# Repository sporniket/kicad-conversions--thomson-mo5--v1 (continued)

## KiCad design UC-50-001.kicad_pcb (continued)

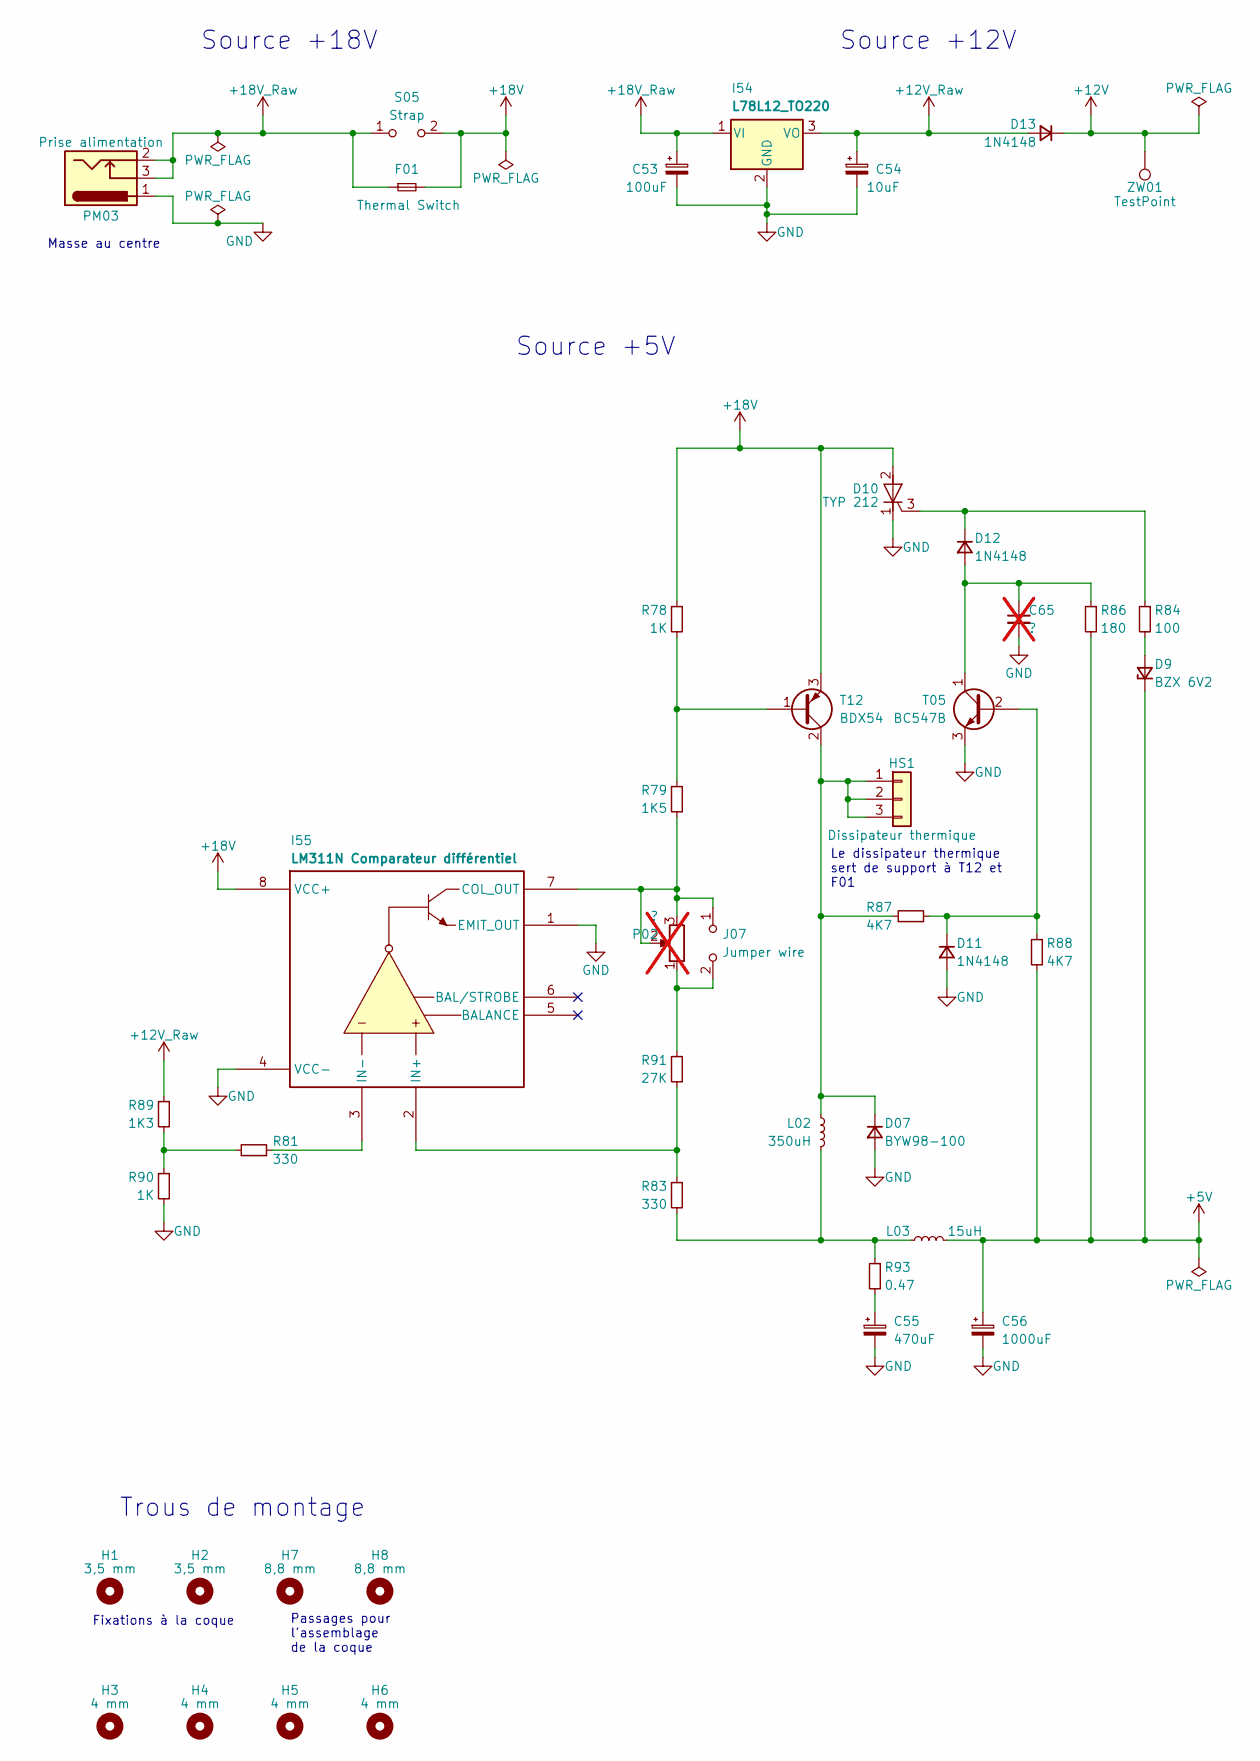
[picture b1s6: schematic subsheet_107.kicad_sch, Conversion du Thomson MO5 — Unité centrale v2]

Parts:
C53: 100uF; Passive_THT_capacitor_polarized_EU_W2.54mm_L5.08mm
C54: 10uF; Passive_THT_capacitor_polarized_EU_W2.54mm_L5.08mm
C55: 470uF; CP_Radial_D10.0mm_P5.00mm
C56: 1000uF; CP_Radial_D13.0mm_P5.00mm
C65: ?; Passive_THT_capacitor_mlcc_W2.54mm_L5.08mm; not fitted
D07: BYW98-100; Passive_THT_diode_power_W5.715mm_L17.78mm
D9: BZX 6V2; Passive_THT_diode_zener_W2.54mm_L12.70mm
D10: TYP 212; TO-220-3_Vertical
D11, D12, D13: 1N4148; Passive_THT_diode_W2.54mm_L12.70mm
F01: Thermal Switch; Passive_THT_thermal_switch_L5.08mm
H1, H2: 3,5 mm; MountingHole_3.5mm_limited_courtyard
H3, H4, H5, H6: 4 mm; MountingHole_4mm_limited_courtyard
H7, H8: 8,8 mm; MountingHole_8.8mm_limited_courtyard
HS1: Dissipateur thermique; Passive_THT_heatsink__power_mosfet_and_thermal_switch
I54: L78L12_TO220; TO-220-3_Vertical
I55: LM311N Comparateur différentiel; DIP-8_W7.62mm_LongPads
J07: Jumper wire; Passive_THT_jumper_wire_W2.54mm_L12.70mm
L02: 350uH; Passive_THT_ferrite_core_inductor_L10.16mm
L03: 15uH; Passive_THT_ferrite_core_inductor_L5.08mm
P02: ?; Potentiometer_ACP_CA9-V10_Vertical_Hole; not fitted
PM03: Prise alimentation; BarrelJack_Horizontal
R78, R90: 1K; Passive_THT_resistor_EU_W2.54mm_L12.70mm
R79: 1K5; Passive_THT_resistor_EU_W2.54mm_L12.70mm
R81, R83: 330; Passive_THT_resistor_EU_W2.54mm_L12.70mm
R84: 100; Passive_THT_resistor_EU_W2.54mm_L12.70mm
R86: 180; Passive_THT_resistor_EU_W2.54mm_L12.70mm
R87, R88: 4K7; Passive_THT_resistor_EU_W2.54mm_L12.70mm
R89: 1K3; Passive_THT_resistor_EU_W2.54mm_L12.70mm
R91: 27K; Passive_THT_resistor_EU_W2.54mm_L12.70mm
R93: 0.47; Passive_THT_resistor_EU_W2.54mm_L12.70mm
S05: Strap; Passive_THT_jumper_wire_W2.54mm_L12.70mm
T05: BC547B; TO-92_Inline_Wide
T12: BDX54; TO-220-3_Vertical
ZW01: TestPoint; PinHeader_1x01_P2.54mm_Vertical

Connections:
+5V: C56.1, D9.1 (K), L03.2, R86.2, R88.2; also elsewhere on the board
+12V: D13.1 (K), ZW01.1; also elsewhere on the board
+12V_Raw: C54.1, D13.2 (A), I54.3 (VO), R89.1
+18V: D10.2 (A), F01.2, I55.8 (VCC+), R78.1, S05.2 (B), T12.3 (E)
+18V_Raw: C53.1, F01.1, I54.1 (VI), PM03.2, PM03.3, S05.1 (A)
GND: C53.2, C54.2, C55.2, C56.2, C65.2, D07.2 (A), D10.1 (K), D11.2 (A), I54.2 (GND), I55.1 (EMIT_OUT), I55.4 (VCC-), PM03.1, R90.2, T05.3 (E); also elsewhere on the board
unnamed: C55.1, R93.2
unnamed: D07.1 (K), HS1.1, HS1.2, HS1.3, L02.1, R87.1, T12.2 (C)
unnamed: D9.2 (A), R84.2
unnamed: D10.3 (G), D12.1 (K), R84.1
unnamed: D11.1 (K), R87.2, R88.1, T05.2 (B)
unnamed: C65.1, D12.2 (A), R86.1, T05.1 (C)
unnamed: I55.7 (COL_OUT), J07.1 (A), P02.2, P02.3, R79.2
unnamed: I55.2 (IN+), R83.1, R91.2
unnamed: I55.3 (IN-), R81.2
unnamed: J07.2 (B), P02.1, R91.1
unnamed: L02.2, L03.1, R83.2, R93.1
unnamed: R81.1, R89.2, R90.1
unnamed: R78.2, R79.1, T12.1 (B)

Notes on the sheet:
Masse au centre
Le dissipateur thermique sert de support à T12 et F01
Source +5V
Trous de montage
Source +12V
Source +18V
Fixations à la coque
Passages pour l'assemblage de la coque

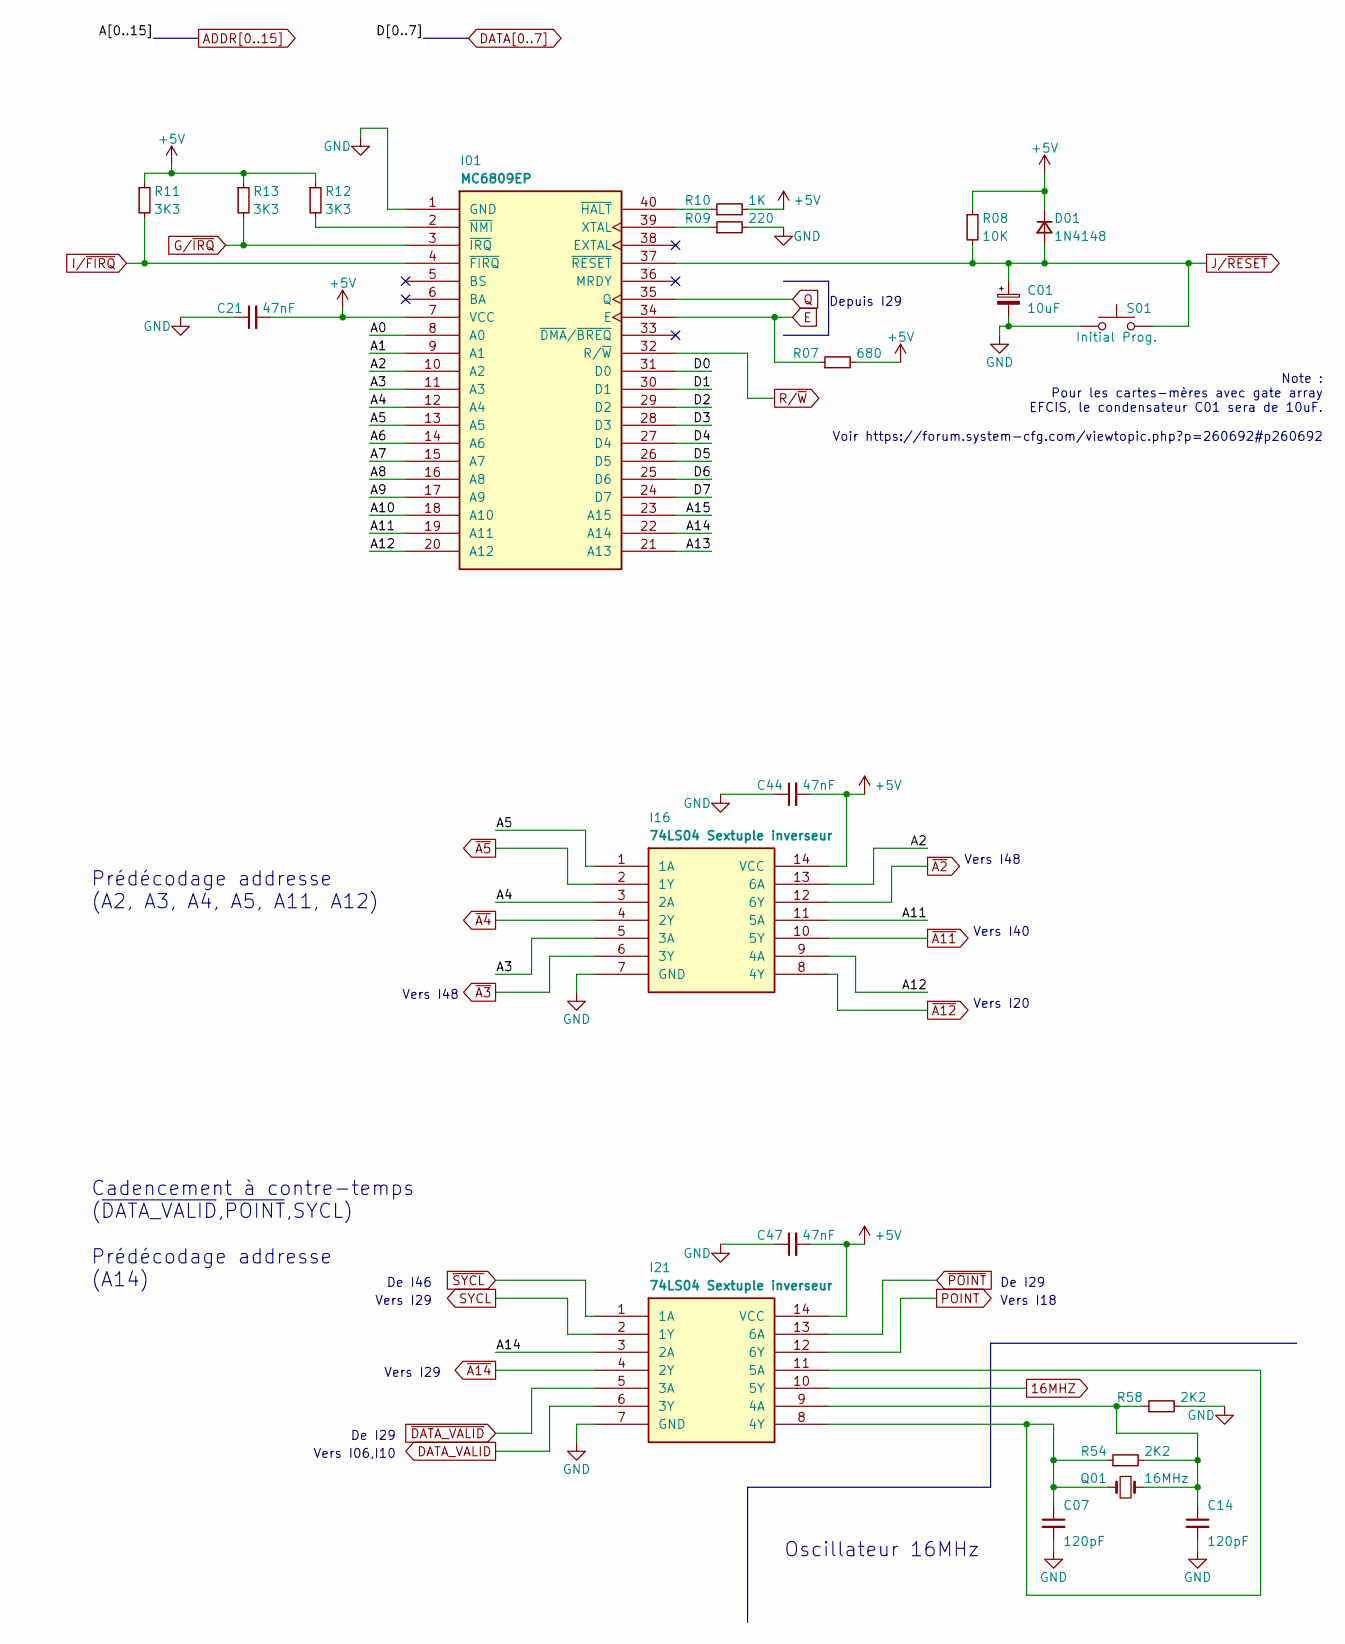
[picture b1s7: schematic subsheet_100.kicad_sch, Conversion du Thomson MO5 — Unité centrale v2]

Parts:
C01: 10uF; Passive_THT_capacitor_polarized_EU_W2.54mm_L5.08mm
C07, C14: 120pF; Passive_THT_capacitor_mlcc_W2.54mm_L5.08mm
C21, C44, C47: 47nF; Passive_THT_capacitor_mlcc_W2.54mm_L5.08mm
D01: 1N4148; Passive_THT_diode_W2.54mm_L12.70mm
I01: MC6809EP; DIP-40_W15.24mm_LongPads
I16, I21: 74LS04 Sextuple inverseur; DIP-14_W7.62mm_LongPads
Q01: 16MHz; Crystal_HC49-U_Horizontal
R07: 680; Passive_THT_resistor_EU_W2.54mm_L12.70mm
R08: 10K; Passive_THT_resistor_EU_W2.54mm_L12.70mm
R09: 220; Passive_THT_resistor_EU_W2.54mm_L12.70mm
R10: 1K; Passive_THT_resistor_EU_W2.54mm_L12.70mm
R11, R12, R13: 3K3; Passive_THT_resistor_EU_W2.54mm_L12.70mm
R54, R58: 2K2; Passive_THT_resistor_EU_W2.54mm_L12.70mm
S01: Initial Prog.; SW_PUSH_6mm_RESET_MO5

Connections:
16MHZ: I21.10 (5Y); also elsewhere on the board
+5V: C21.2, C44.2, C47.2, D01.1 (K), I01.7 (VCC), I16.14 (VCC), I21.14 (VCC), R07.2, R08.1, R10.2, R11.1, R12.1, R13.1; also elsewhere on the board
ADDR0: I01.8 (A0); also elsewhere on the board
ADDR1: I01.9 (A1); also elsewhere on the board
ADDR2: I01.10 (A2), I16.13 (6A); also elsewhere on the board
ADDR3: I01.11 (A3), I16.5 (3A); also elsewhere on the board
ADDR4: I01.12 (A4), I16.3 (2A); also elsewhere on the board
ADDR5: I01.13 (A5), I16.1 (1A); also elsewhere on the board
ADDR6: I01.14 (A6); also elsewhere on the board
ADDR7: I01.15 (A7); also elsewhere on the board
ADDR8: I01.16 (A8); also elsewhere on the board
ADDR9: I01.17 (A9); also elsewhere on the board
ADDR10: I01.18 (A10); also elsewhere on the board
ADDR11: I01.19 (A11), I16.11 (5A); also elsewhere on the board
ADDR12: I01.20 (A12), I16.9 (4A); also elsewhere on the board
ADDR13: I01.21 (A13); also elsewhere on the board
ADDR14: I01.22 (A14), I21.3 (2A); also elsewhere on the board
ADDR15: I01.23 (A15); also elsewhere on the board
DATA0: I01.31 (D0); also elsewhere on the board
DATA1: I01.30 (D1); also elsewhere on the board
DATA2: I01.29 (D2); also elsewhere on the board
DATA3: I01.28 (D3); also elsewhere on the board
DATA4: I01.27 (D4); also elsewhere on the board
DATA5: I01.26 (D5); also elsewhere on the board
DATA6: I01.25 (D6); also elsewhere on the board
DATA7: I01.24 (D7); also elsewhere on the board
DATA_VALID: I21.6 (3Y); also elsewhere on the board
E: I01.34 (E), R07.1; also elsewhere on the board
GND: C01.2, C07.2, C14.2, C21.1, C44.1, C47.1, I01.1 (GND), I16.7 (GND), I21.7 (GND), R09.2, R58.2, S01.1; also elsewhere on the board
G/~IRQ: I01.3 (~IRQ), R13.2; also elsewhere on the board
I/~FIRQ: I01.4 (~FIRQ), R11.2; also elsewhere on the board
J/~RESET: C01.1, D01.2 (A), I01.37 (~RESET), R08.2, S01.2; also elsewhere on the board
unnamed: I01.39 (XTAL), R09.1
unnamed: I01.40 (~HALT), R10.1
unnamed: I01.2 (~NMI), R12.2
unnamed: C14.1, I21.9 (4A), Q01.1, R54.2, R58.1
unnamed: C07.1, I21.8 (4Y), I21.11 (5A), Q01.2, R54.1
POINT: I21.12 (6Y); also elsewhere on the board
Q: I01.35 (Q); also elsewhere on the board
R/~W: I01.32 (R/~W); also elsewhere on the board
SYCL: I21.2 (1Y); also elsewhere on the board
~A2: I16.12 (6Y); also elsewhere on the board
~A3: I16.6 (3Y); also elsewhere on the board
~A4: I16.4 (2Y); also elsewhere on the board
~A5: I16.2 (1Y); also elsewhere on the board
~A11: I16.10 (5Y); also elsewhere on the board
~A12: I16.8 (4Y); also elsewhere on the board
~A14: I21.4 (2Y); also elsewhere on the board
~DATA_VALID: I21.5 (3A); also elsewhere on the board
~POINT: I21.13 (6A); also elsewhere on the board
~SYCL: I21.1 (1A); also elsewhere on the board

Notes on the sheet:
De I46
Vers I29
Vers I48
Vers I20
Oscillateur 16MHz
De I29
Cadencement à contre-temps (~{DATA_VALID},~{POINT},SYCL) Prédécodage addresse (A14)
Vers I06,I10
Note : Pour les cartes-mères avec gate array EFCIS, le condensateur C01 sera de 10uF. Voir https://forum.system-cfg.com/viewtopic.php?p=260692#p260692
Vers I40
Prédécodage addresse (A2, A3, A4, A5, A11, A12)
Depuis I29
Vers I18

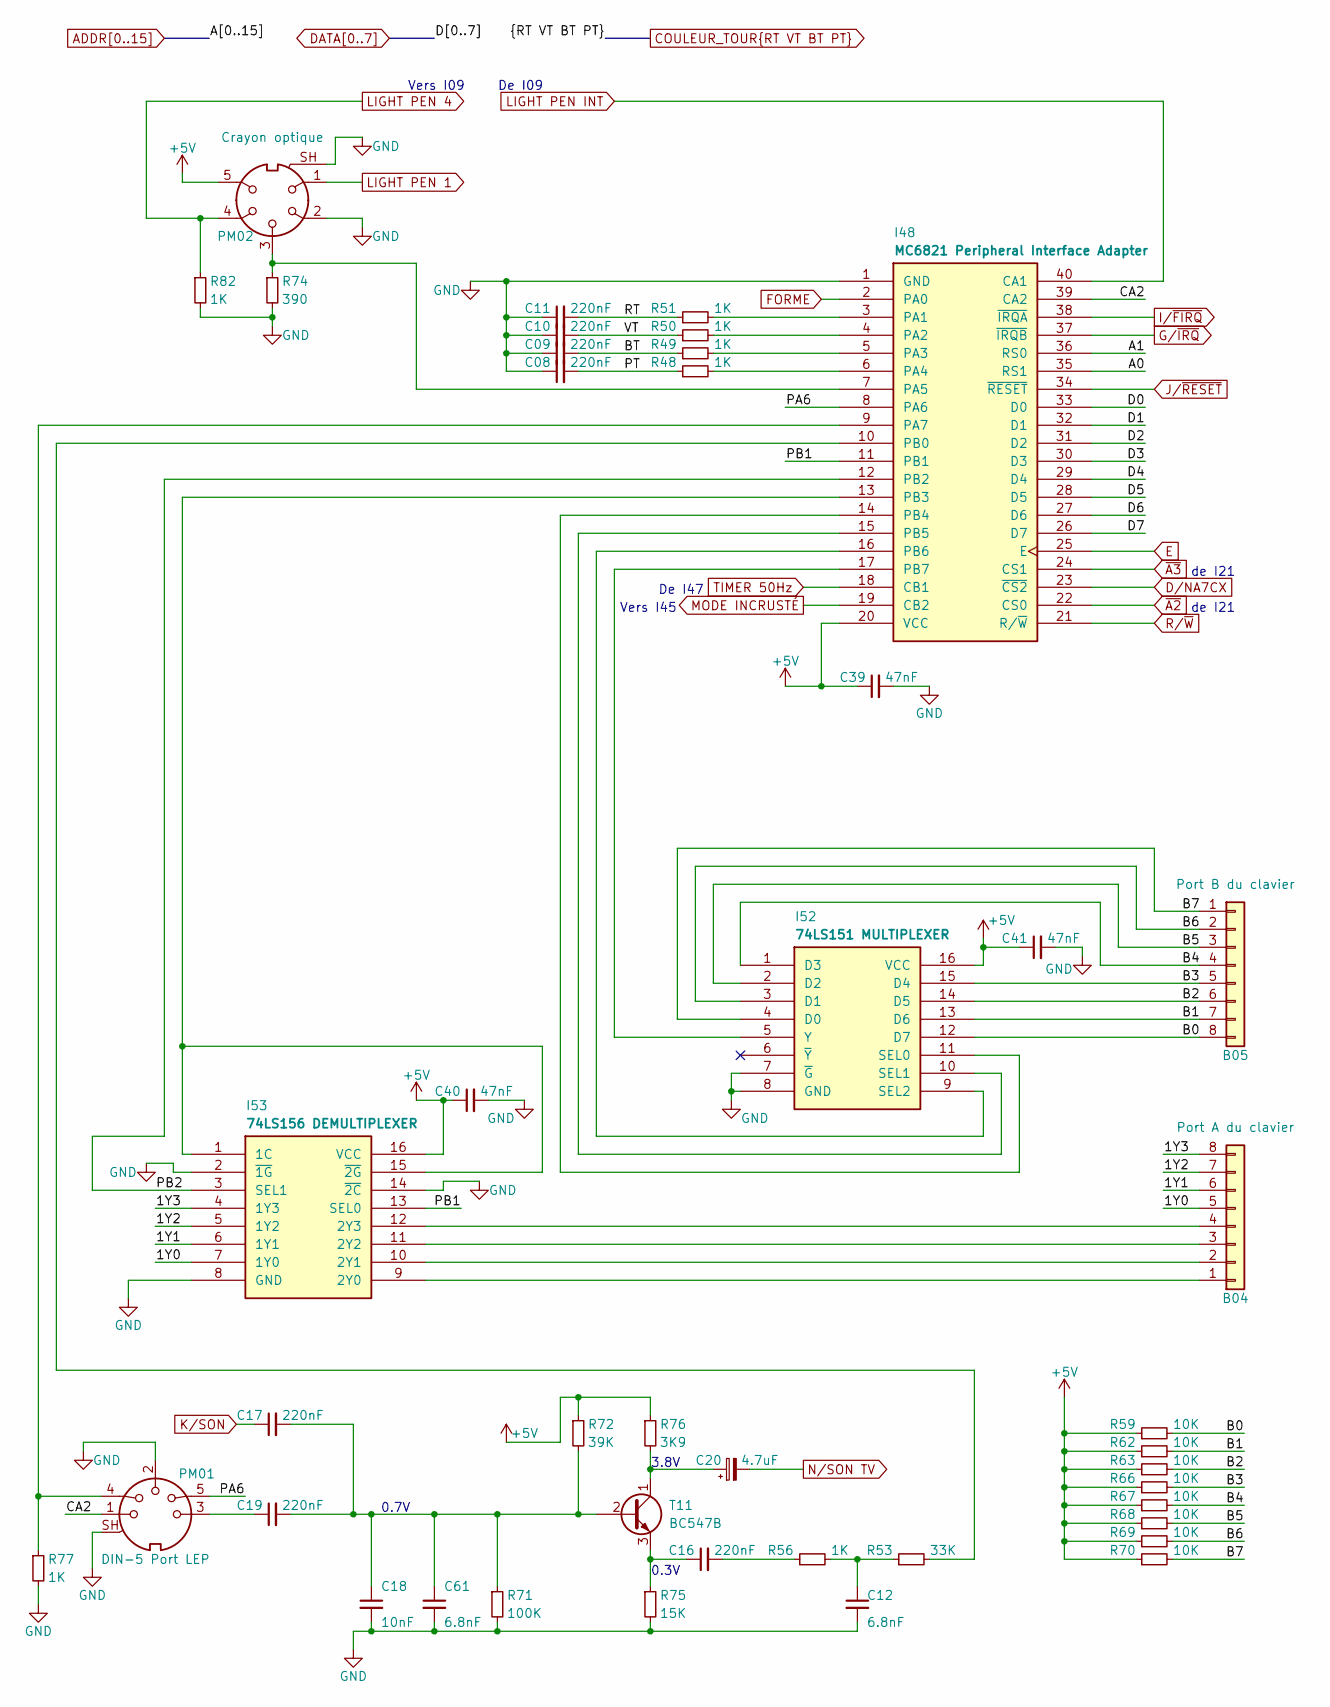
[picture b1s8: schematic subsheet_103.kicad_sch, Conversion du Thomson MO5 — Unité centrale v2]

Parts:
B04: Port A du clavier; FFC_FPC_Connector_1x08_P2.54mm_THT_Vertical
B05: Port B du clavier; FFC_FPC_Connector_1x08_P2.54mm_THT_Vertical
C08, C09, C10, C11, C16, C17, C19: 220nF; Passive_THT_capacitor_mlcc_W2.54mm_L5.08mm
C12, C61: 6.8nF; Passive_THT_capacitor_mlcc_W2.54mm_L5.08mm
C18: 10nF; Passive_THT_capacitor_mlcc_W2.54mm_L5.08mm
C20: 4.7uF; Passive_THT_capacitor_polarized_EU_W2.54mm_L5.08mm
C39, C40, C41: 47nF; Passive_THT_capacitor_mlcc_W2.54mm_L5.08mm
I48: MC6821 Peripheral Interface Adapter; DIP-40_W15.24mm_LongPads
I52: 74LS151 MULTIPLEXER; DIP-16_W7.62mm_LongPads
I53: 74LS156 DEMULTIPLEXER; DIP-16_W7.62mm_LongPads
PM01: DIN-5 Port LEP; DIN_41524_Receptacle_5_pole_180_degrees_Shielded
PM02: Crayon optique; DIN_45322_Receptacle_5_pole_240_degrees_Shielded_Ordered_pi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
R48, R49, R50, R51, R56, R77, R82: 1K; Passive_THT_resistor_EU_W2.54mm_L12.70mm
R53: 33K; Passive_THT_resistor_EU_W2.54mm_L12.70mm
R59, R62, R63, R66, R67, R68, R69, R70: 10K; Passive_THT_resistor_EU_W2.54mm_L12.70mm
R71: 100K; Passive_THT_resistor_EU_W2.54mm_L12.70mm
R72: 39K; Passive_THT_resistor_EU_W2.54mm_L12.70mm
R74: 390; Passive_THT_resistor_EU_W2.54mm_L12.70mm
R75: 15K; Passive_THT_resistor_EU_W2.54mm_L12.70mm
R76: 3K9; Passive_THT_resistor_EU_W2.54mm_L12.70mm
T11: BC547B; TO-92_Inline_Wide

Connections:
+5V: C39.1, C40.1, C41.1, I48.20 (VCC), I52.16 (VCC), I53.16 (VCC), PM02.5, R59.1, R62.1, R63.1, R66.1, R67.1, R68.1, R69.1, R70.1, R72.1, R76.1; also elsewhere on the board
/I48–MC6821P ; I52–53–B04–B05–ports clavier ; PM01–LEP ; PM02–Crayon optique/1Y0: B04.5, I53.7 (1Y0)
/I48–MC6821P ; I52–53–B04–B05–ports clavier ; PM01–LEP ; PM02–Crayon optique/1Y1: B04.6, I53.6 (1Y1)
/I48–MC6821P ; I52–53–B04–B05–ports clavier ; PM01–LEP ; PM02–Crayon optique/1Y2: B04.7, I53.5 (1Y2)
/I48–MC6821P ; I52–53–B04–B05–ports clavier ; PM01–LEP ; PM02–Crayon optique/1Y3: B04.8, I53.4 (1Y3)
/I48–MC6821P ; I52–53–B04–B05–ports clavier ; PM01–LEP ; PM02–Crayon optique/B0: B05.8, I52.12 (D7), R59.2
/I48–MC6821P ; I52–53–B04–B05–ports clavier ; PM01–LEP ; PM02–Crayon optique/B1: B05.7, I52.13 (D6), R62.2
/I48–MC6821P ; I52–53–B04–B05–ports clavier ; PM01–LEP ; PM02–Crayon optique/B2: B05.6, I52.14 (D5), R63.2
/I48–MC6821P ; I52–53–B04–B05–ports clavier ; PM01–LEP ; PM02–Crayon optique/B3: B05.5, I52.15 (D4), R66.2
/I48–MC6821P ; I52–53–B04–B05–ports clavier ; PM01–LEP ; PM02–Crayon optique/B4: B05.4, I52.1 (D3), R67.2
/I48–MC6821P ; I52–53–B04–B05–ports clavier ; PM01–LEP ; PM02–Crayon optique/B5: B05.3, I52.2 (D2), R68.2
/I48–MC6821P ; I52–53–B04–B05–ports clavier ; PM01–LEP ; PM02–Crayon optique/B6: B05.2, I52.3 (D1), R69.2
/I48–MC6821P ; I52–53–B04–B05–ports clavier ; PM01–LEP ; PM02–Crayon optique/B7: B05.1, I52.4 (D0), R70.2
/I48–MC6821P ; I52–53–B04–B05–ports clavier ; PM01–LEP ; PM02–Crayon optique/CA2: I48.39 (CA2), PM01.1
/I48–MC6821P ; I52–53–B04–B05–ports clavier ; PM01–LEP ; PM02–Crayon optique/PA6: I48.8 (PA6), PM01.5
/I48–MC6821P ; I52–53–B04–B05–ports clavier ; PM01–LEP ; PM02–Crayon optique/PB1: I48.11 (PB1), I53.13 (SEL0)
/I48–MC6821P ; I52–53–B04–B05–ports clavier ; PM01–LEP ; PM02–Crayon optique/PB2: I48.12 (PB2), I53.3 (SEL1)
ADDR0: I48.35 (RS1); also elsewhere on the board
ADDR1: I48.36 (RS0); also elsewhere on the board
COULEUR_TOUR.BT: C09.2, R49.1; also elsewhere on the board
COULEUR_TOUR.PT: C08.2, R48.1; also elsewhere on the board
COULEUR_TOUR.RT: C11.2, R51.1; also elsewhere on the board
COULEUR_TOUR.VT: C10.2, R50.1; also elsewhere on the board
DATA0: I48.33 (D0); also elsewhere on the board
DATA1: I48.32 (D1); also elsewhere on the board
DATA2: I48.31 (D2); also elsewhere on the board
DATA3: I48.30 (D3); also elsewhere on the board
DATA4: I48.29 (D4); also elsewhere on the board
DATA5: I48.28 (D5); also elsewhere on the board
DATA6: I48.27 (D6); also elsewhere on the board
DATA7: I48.26 (D7); also elsewhere on the board
D/NA7CX: I48.23 (~CS2); also elsewhere on the board
E: I48.25 (E); also elsewhere on the board
FORME: I48.2 (PA0); also elsewhere on the board
GND: C08.1, C09.1, C10.1, C11.1, C12.2, C18.2, C39.2, C40.2, C41.2, C61.2, I48.1 (GND), I52.7 (~G), I52.8 (GND), I53.2 (~1G), I53.8 (GND), I53.14 (~2C), PM01.2, PM01.SH, PM02.2, PM02.SH, R71.2, R74.2, R75.2, R77.2, R82.2; also elsewhere on the board
G/~IRQ: I48.37 (~IRQB); also elsewhere on the board
I/~FIRQ: I48.38 (~IRQA); also elsewhere on the board
J/~RESET: I48.34 (~RESET); also elsewhere on the board
K/SON: C17.1; also elsewhere on the board
LIGHT PEN 1: PM02.1; also elsewhere on the board
LIGHT PEN 4: PM02.4, R82.1; also elsewhere on the board
LIGHT PEN INT: I48.40 (CA1); also elsewhere on the board
MODE INCRUSTÉ: I48.19 (CB2); also elsewhere on the board
unnamed: B04.1, I53.9 (2Y0)
unnamed: B04.2, I53.10 (2Y1)
unnamed: B04.3, I53.11 (2Y2)
unnamed: B04.4, I53.12 (2Y3)
unnamed: C12.1, R53.1, R56.2
unnamed: C16.2, R56.1
unnamed: C19.1, PM01.3
unnamed: I48.3 (PA1), R51.2
unnamed: I48.4 (PA2), R50.2
unnamed: I48.5 (PA3), R49.2
unnamed: I48.6 (PA4), R48.2
unnamed: I48.7 (PA5), PM02.3, R74.1
unnamed: I48.9 (PA7), PM01.4, R77.1
unnamed: I48.10 (PB0), R53.2
unnamed: I48.13 (PB3), I53.1 (1C), I53.15 (~2G)
unnamed: I48.14 (PB4), I52.11 (SEL0)
unnamed: I48.15 (PB5), I52.10 (SEL1)
unnamed: I48.16 (PB6), I52.9 (SEL2)
unnamed: I48.17 (PB7), I52.5 (Y)
unnamed: C17.2, C18.1, C19.2, C61.1, R71.1, R72.2, T11.2 (B)
unnamed: C20.1, R76.2, T11.1 (C)
unnamed: C16.1, R75.1, T11.3 (E)
N/SON TV: C20.2; also elsewhere on the board
R/~W: I48.21 (R/~W); also elsewhere on the board
TIMER 50Hz: I48.18 (CB1); also elsewhere on the board
~A2: I48.22 (CS0); also elsewhere on the board
~A3: I48.24 (CS1); also elsewhere on the board

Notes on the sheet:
de I21
0.3V
De I47
3.8V
0.7V
Vers I45
Vers I09
De I09

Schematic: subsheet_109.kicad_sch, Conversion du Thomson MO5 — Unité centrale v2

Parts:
I100, I101, I102: 16 Kio RAM; PinSocket_1x21_P2.54mm_Vertical

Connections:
+5V: I100.9 (VCC), I101.9 (VCC), I102.9 (VCC); also elsewhere on the board
CLDATA0: I101.12 (D0); also elsewhere on the board
CLDATA1: I101.16 (D1); also elsewhere on the board
CLDATA2: I101.15 (D2); also elsewhere on the board
CLDATA3: I101.14 (D3); also elsewhere on the board
CLDATA4: I101.10 (D4); also elsewhere on the board
CLDATA5: I101.11 (D5); also elsewhere on the board
CLDATA6: I101.3 (D6); also elsewhere on the board
CLDATA7: I101.2 (D7); also elsewhere on the board
DATA0: I100.12 (D0); also elsewhere on the board
DATA1: I100.16 (D1); also elsewhere on the board
DATA2: I100.15 (D2); also elsewhere on the board
DATA3: I100.14 (D3); also elsewhere on the board
DATA4: I100.10 (D4); also elsewhere on the board
DATA5: I100.11 (D5); also elsewhere on the board
DATA6: I100.3 (D6); also elsewhere on the board
DATA7: I100.2 (D7); also elsewhere on the board
GND: I100.13 (GND), I101.13 (GND), I102.13 (GND); also elsewhere on the board
MADDR0: I100.17 (MA0), I101.17 (MA0), I102.17 (MA0); also elsewhere on the board
MADDR1: I100.18 (MA1), I101.18 (MA1), I102.18 (MA1); also elsewhere on the board
MADDR2: I100.19 (MA2), I101.19 (MA2), I102.19 (MA2); also elsewhere on the board
MADDR3: I100.20 (MA3), I101.20 (MA3), I102.20 (MA3); also elsewhere on the board
MADDR4: I100.8 (MA4), I101.8 (MA4), I102.8 (MA4); also elsewhere on the board
MADDR5: I100.7 (MA5), I101.7 (MA5), I102.7 (MA5); also elsewhere on the board
MADDR6: I100.6 (MA6), I101.6 (MA6), I102.6 (MA6); also elsewhere on the board
MADDR7: I100.21 (MA7), I101.21 (MA7), I102.21 (MA7); also elsewhere on the board
PTDATA0: I102.12 (D0); also elsewhere on the board
PTDATA1: I102.16 (D1); also elsewhere on the board
PTDATA2: I102.15 (D2); also elsewhere on the board
PTDATA3: I102.14 (D3); also elsewhere on the board
PTDATA4: I102.10 (D4); also elsewhere on the board
PTDATA5: I102.11 (D5); also elsewhere on the board
PTDATA6: I102.3 (D6); also elsewhere on the board
PTDATA7: I102.2 (D7); also elsewhere on the board
~CAS_COL: I101.1 (~CAS); also elsewhere on the board
~CAS_EXT: I100.1 (~CAS); also elsewhere on the board
~CAS_PT: I102.1 (~CAS); also elsewhere on the board
~NRAS: I100.5 (~RAS), I101.5 (~RAS), I102.5 (~RAS); also elsewhere on the board
~RAMW: I100.4 (~W), I101.4 (~W), I102.4 (~W); also elsewhere on the board

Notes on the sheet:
I102 peut être installé à la place de I19/I23. Dans ce cas C31 n'est pas installé.
De I12
Extension
Couleur
De I29
I101 peut être installé à la place de I08/I11. Dans ce cas C27 n'est pas installé.
I100 peut être installé à la place de I02/I05. Dans ce cas C23 n'est pas installé.
Point
De I09
Les modules mémoire I100, I101 et I102 sont implantables uniquement sur les révisions POP 5007S et POP 5009S de la carte-mère.

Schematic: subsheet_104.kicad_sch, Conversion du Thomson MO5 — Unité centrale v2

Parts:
B01: Connecteur extension (dessous); extension_port_1x19_backside_1.5mm_pad_width_2.54mm_pad_pit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
B02: Connecteur extension (dessus); extension_port_1x19_topside_1.5mm_pad_width_2.54mm_pad_pitch
B06: Port cartouche (rangée 'a' vers le nord); cartridge_port_2x13_pcb_edge_pitch_100mils_row_pitch_200mils
C25, C64: 47nF; Passive_THT_capacitor_mlcc_W2.54mm_L5.08mm
I04: M27128A 16k×8 EPROM; DIP-28_W15.24mm_LongPads
I56: 2732 4k×8 EPROM; DIP-24_W15.24mm_LongPads
ZW02: TestPoint; PinHeader_1x01_P2.54mm_Vertical

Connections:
+5V: B02.19, B06.b2, C25.2, C64.2, I04.1 (VPP), I04.27 (~P), I04.28 (VCC), I56.24 (VCC); also elsewhere on the board
+12V: B01.1, ZW02.1; also elsewhere on the board
ADDR0: B02.16, B06.a14, I04.10 (A0), I56.8 (A0); also elsewhere on the board
ADDR1: B02.15, B06.a13, I04.9 (A1), I56.7 (A1); also elsewhere on the board
ADDR2: B02.14, B06.a12, I04.8 (A2), I56.6 (A2); also elsewhere on the board
ADDR3: B02.13, B06.a11, I04.7 (A3), I56.5 (A3); also elsewhere on the board
ADDR4: B02.12, B06.a10, I04.6 (A4), I56.4 (A4); also elsewhere on the board
ADDR5: B02.11, B06.a9, I04.5 (A5), I56.3 (A5); also elsewhere on the board
ADDR6: B02.10, B06.a8, I04.4 (A6), I56.2 (A6); also elsewhere on the board
ADDR7: B02.9, B06.a7, I04.3 (A7), I56.1 (A7); also elsewhere on the board
ADDR8: B02.8, B06.a6, I04.25 (A8), I56.23 (A8); also elsewhere on the board
ADDR9: B02.7, B06.a5, I04.24 (A9), I56.22 (A9); also elsewhere on the board
ADDR10: B02.6, B06.a4, I04.21 (A10), I56.19 (A10); also elsewhere on the board
ADDR11: B02.5, B06.a3, I04.23 (A11), I56.21 (A11); also elsewhere on the board
ADDR12: B06.a2, I04.2 (A12); also elsewhere on the board
ADDR13: B06.b4, I04.26 (A13); also elsewhere on the board
ADDR14: B06.b1; also elsewhere on the board
ADDR15: B06.a1; also elsewhere on the board
A/SYNLT: B02.18; also elsewhere on the board
B/NBXXX: B02.17; also elsewhere on the board
C/NAXXX: B02.4; also elsewhere on the board
DATA0: B01.13, B06.b13, I04.11 (Q0), I56.9 (Q0); also elsewhere on the board
DATA1: B01.12, B06.b12, I04.12 (Q1), I56.10 (Q1); also elsewhere on the board
DATA2: B01.11, B06.b11, I04.13 (Q2), I56.11 (Q2); also elsewhere on the board
DATA3: B01.10, B06.b10, I04.15 (Q3), I56.13 (Q3); also elsewhere on the board
DATA4: B01.9, B06.b9, I04.16 (Q4), I56.14 (Q4); also elsewhere on the board
DATA5: B01.8, B06.b8, I04.17 (Q5), I56.15 (Q5); also elsewhere on the board
DATA6: B01.7, B06.b7, I04.18 (Q6), I56.16 (Q6); also elsewhere on the board
DATA7: B01.6, B06.b6, I04.19 (Q7), I56.17 (Q7); also elsewhere on the board
D/NA7CX: B02.3; also elsewhere on the board
E: B01.5, B06.a15; also elsewhere on the board
E/CLRG: B02.2; also elsewhere on the board
F/VIDEO: B01.18; also elsewhere on the board
GND: B01.2, B02.1, B06.b14, C25.1, C64.1, I04.14 (GND), I56.12 (GND); also elsewhere on the board
G/~IRQ: B01.17; also elsewhere on the board
H/VCO-16MHz: B01.16; also elsewhere on the board
I/~FIRQ: B01.15; also elsewhere on the board
J/~RESET: B01.14; also elsewhere on the board
K/SON: B01.3; also elsewhere on the board
L/~CSCART: B06.b5; also elsewhere on the board
M/PRCART: B06.b3; also elsewhere on the board
R/~W: B01.4, B06.b15; also elsewhere on the board
~CS_EPROM_2: I56.18 (~E), I56.20 (~G/VPP); also elsewhere on the board
~CS_EPROM: I04.20 (~E), I04.22 (~G); also elsewhere on the board

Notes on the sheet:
De I27
De I14
Vers I32
Vers I46
Les broches 1 sont à gauche
Vers C17 (mélangeur audio LEP)
De I20
De I29

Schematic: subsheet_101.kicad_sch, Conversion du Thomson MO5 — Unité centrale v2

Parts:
C37, C70: 47nF; Passive_THT_capacitor_mlcc_W2.54mm_L5.08mm
C60: 100pF; Passive_THT_capacitor_mlcc_W2.54mm_L5.08mm
C6000: 220pF; Passive_THT_capacitor_mlcc_W2.54mm_L5.08mm
I29: GATE_ARRAY_MO5_V2_PHY; PLCC-68_THT-Socket
J03, J04: Jumper wire; Passive_THT_jumper_wire_W2.54mm_L10.16mm
R94: 100K; Passive_THT_resistor_EU_W2.54mm_L12.70mm

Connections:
+5V: C37.1, C70.1, I29.2 (VCC), J03.2; also elsewhere on the board
ADDR0: I29.25 (A0); also elsewhere on the board
ADDR1: I29.24 (A1); also elsewhere on the board
ADDR2: I29.23 (A2); also elsewhere on the board
ADDR3: I29.22 (A3); also elsewhere on the board
ADDR4: I29.21 (A4); also elsewhere on the board
ADDR5: I29.20 (A5); also elsewhere on the board
ADDR6: I29.19 (A6); also elsewhere on the board
ADDR7: I29.16 (A7); also elsewhere on the board
ADDR8: I29.15 (A8); also elsewhere on the board
ADDR9: I29.14 (A9); also elsewhere on the board
ADDR10: I29.13 (A10); also elsewhere on the board
ADDR11: I29.12 (A11); also elsewhere on the board
ADDR12: I29.11 (A12); also elsewhere on the board
ADDR13: I29.49 (A13); also elsewhere on the board
ADDR15: I29.47 (A15); also elsewhere on the board
A/SYNLT: I29.63 (SYNLT); also elsewhere on the board
DATA0: I29.33 (D0); also elsewhere on the board
DATA1: I29.32 (D1); also elsewhere on the board
DATA2: I29.31 (D2); also elsewhere on the board
DATA3: I29.30 (D3); also elsewhere on the board
DATA4: I29.29 (D4); also elsewhere on the board
DATA5: I29.28 (D5); also elsewhere on the board
DATA6: I29.27 (D6); also elsewhere on the board
DATA7: I29.26 (D7); also elsewhere on the board
E: I29.41 (E); also elsewhere on the board
FORME: I29.51 (FORME); also elsewhere on the board
GND: C37.2, C60.2, C6000.2, I29.35 (GND), I29.53 (E_EXT_2), I29.60 (E_EXT), I29.68 (~CS), J04.1, R94.2; also elsewhere on the board
H16: I29.46 (H16); also elsewhere on the board
MADDR0: I29.5 (MA0); also elsewhere on the board
MADDR1: I29.4 (MA1); also elsewhere on the board
MADDR2: I29.3 (MA2); also elsewhere on the board
MADDR3: I29.67 (MA3); also elsewhere on the board
MADDR4: I29.10 (MA4); also elsewhere on the board
MADDR5: I29.9 (MA5); also elsewhere on the board
MADDR6: I29.8 (MA6); also elsewhere on the board
MADDR7: I29.7 (MA7); also elsewhere on the board
unnamed: I29.36 (625/~525), J03.1, J04.2
unnamed: C70.2, I29.57 (SYCL1), R94.1
Q: I29.42 (Q); also elsewhere on the board
R/~W: I29.39 (R/~W); also elsewhere on the board
SYCL: I29.58 (SYCL2); also elsewhere on the board
~A14: I29.48 (A14); also elsewhere on the board
~CAS_COL: I29.65 (~CAS_COL); also elsewhere on the board
~CAS_EXT: I29.64 (~CAS_EXT); also elsewhere on the board
~CAS_PT: I29.66 (~CAS_PT); also elsewhere on the board
~CKLP: I29.37 (~CKLP); also elsewhere on the board
~CS_COL: I29.54 (~CS_COL); also elsewhere on the board
~CS_EXT: I29.56 (~CS_EXT); also elsewhere on the board
~CS_PT: I29.55 (~CS_PT); also elsewhere on the board
~DATA_VALID: I29.44 (~DATA_VALID); also elsewhere on the board
~E: I29.40 (~E); also elsewhere on the board
~INILT: C60.1, C6000.1, I29.62 (~INILT); also elsewhere on the board
~POINT: I29.45 (~POINT); also elsewhere on the board
~RAS: I29.50 (~RAS); also elsewhere on the board
~SUPLT: I29.61 (~SUPLT); also elsewhere on the board

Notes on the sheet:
Depuis I14
Depuis I16
ATTENTION : Les seules broches d'alimentation connectées sont la broche 2 (VCC) et la broche 35 (GND) Les broches 1 et 17 (GND) et les broches 18 et 52 (VCC) sont laissés flottantes. Semble cohérent avec la photo du silicon annotée par furrtek https://github.com/furrtek/SiliconRE/blob/master/Misc/E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
De I21-2
— Fermer J03 seulement pour le mode 625 lignes — Fermer J04 seulement pour le mode 525 lignes
Le gate-array Matra-Harris MA4-Q1200 est interchangeable avec le gate-array EFCIS EFG-J033-E, MAIS nécessite un condensateur de 220pF supplémentaire. Ce condensateur "60bis" est installé entre une via de la piste et une via de la masse juste au sud-est de I25. (POP 5007S, POP 5009S)
